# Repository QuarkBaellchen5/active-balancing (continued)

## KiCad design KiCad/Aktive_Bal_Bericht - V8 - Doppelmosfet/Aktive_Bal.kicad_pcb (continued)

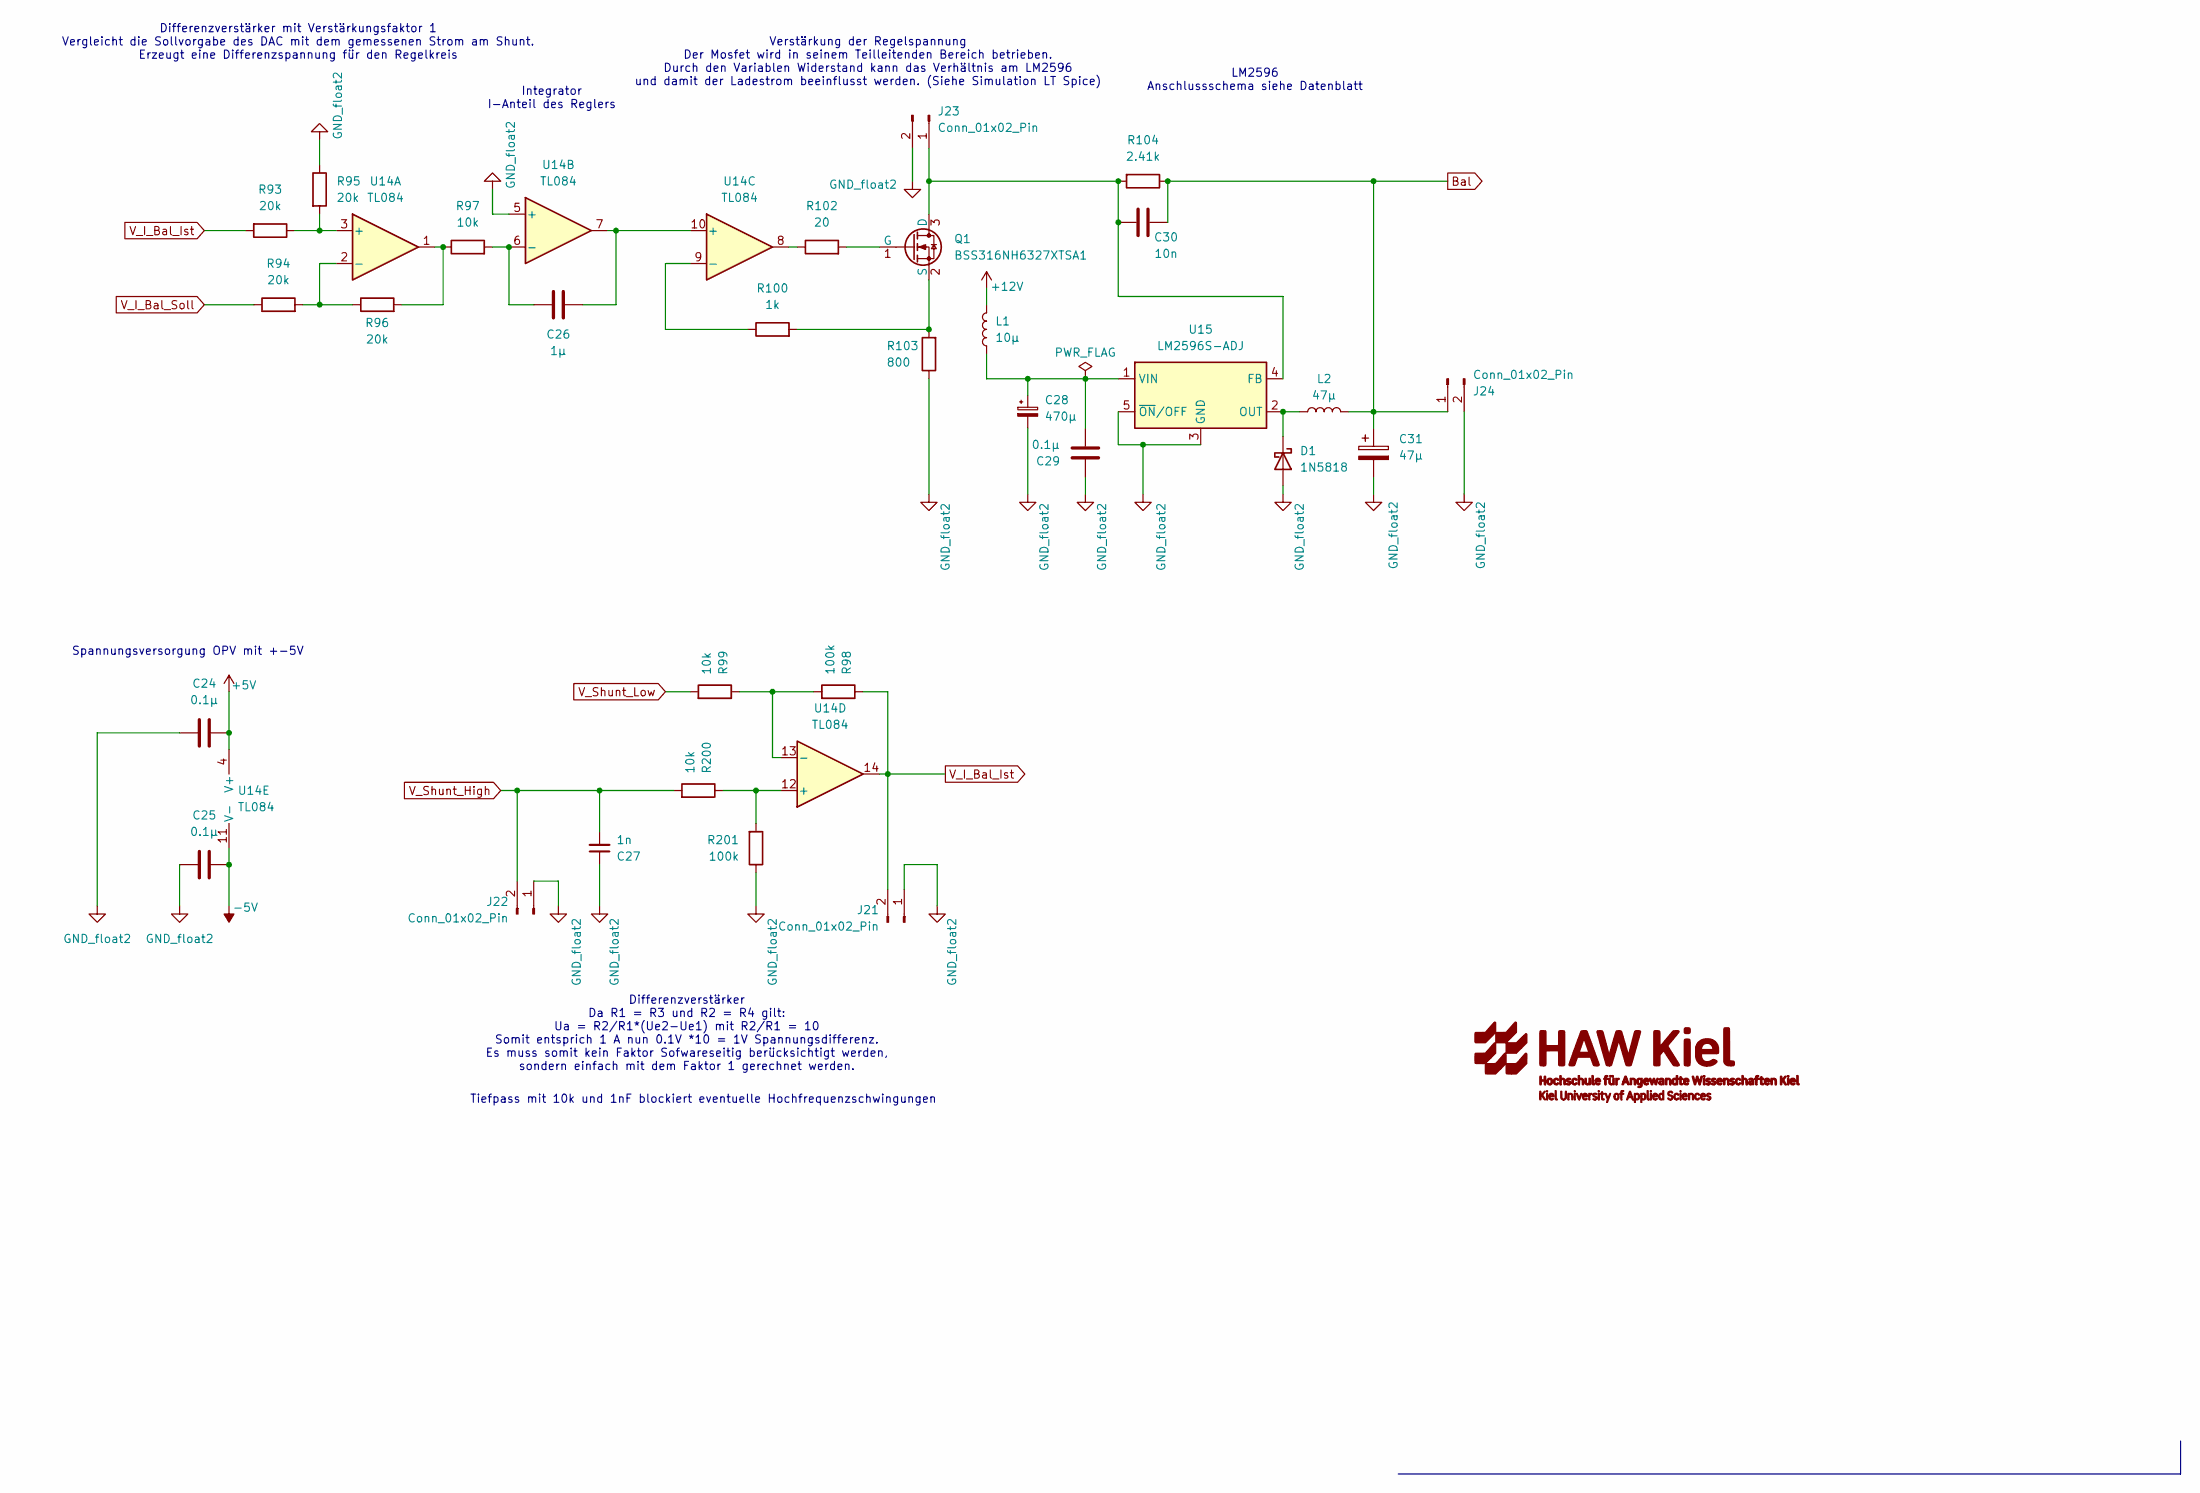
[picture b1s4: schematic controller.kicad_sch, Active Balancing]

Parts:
C24, C25, C29: 0.1µ; C_0805_2012Metric
C26: 1µ; C_0805_2012Metric
C27: 1n; C_0805_2012Metric
C28: 470µ; C_Elec_8x10.2
C30: 10n; C_0805_2012Metric
C31: 47µ; CP_Elec_5x5.3
D1: 1N5818; D_SMA
J21, J22, J23, J24: Conn_01x02_Pin; PinHeader_1x02_P2.54mm_Vertical
L1: 10µ; NRS6045
L2: 47µ; L_Bourns_SRR1260
Q1: BSS316NH6327XTSA1; SOT-23
R93, R94, R95, R96: 20k; R_0805_2012Metric
R97, R99, R200: 10k; R_0805_2012Metric
R98, R201: 100k; R_0805_2012Metric
R100: 1k; R_0805_2012Metric
R102: 20; R_0805_2012Metric
R103: 800; R_0805_2012Metric
R104: 2.41k; R_0805_2012Metric
U14: TL084; SOIC-14_3.9x8.7mm_P1.27mm
U15: LM2596S-ADJ; LM2596_5T

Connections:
+5V: C24.2, U14.4 (V+); also elsewhere on the board
+12V: L1.1; also elsewhere on the board
-5V: C25.2, U14.11 (V-); also elsewhere on the board
Bal: C30.2, C31.1, J24.1, L2.2, R104.1; also elsewhere on the board
GND_float2: C24.1, C25.1, C27.1, C28.2, C29.1, C31.2, D1.2 (A), J21.1, J22.1, J23.2, J24.2, R95.1, R103.1, R201.1, U14.5 (+), U15.3 (GND), U15.5 (~ON/OFF); also elsewhere on the board
unnamed: D1.1 (K), L2.1, U15.2 (OUT)
unnamed: C30.1, J23.1, Q1.3 (D), R104.2, U15.4 (FB)
unnamed: Q1.1 (G), R102.2
unnamed: Q1.2 (S), R100.2, R103.2
unnamed: R96.2, R97.1, U14.1
unnamed: R102.1, U14.8
unnamed: R93.1, R95.2, U14.3 (+)
unnamed: R94.2, R96.1, U14.2 (-)
unnamed: C26.1, R97.2, U14.6 (-)
unnamed: C26.2, U14.7, U14.10 (+)
unnamed: R100.1, U14.9 (-)
unnamed: R200.1, R201.2, U14.12 (+)
unnamed: R98.2, R99.1, U14.13 (-)
unnamed: C28.1, C29.2, L1.2, U15.1 (VIN)
V_I_Bal_Ist: J21.2, R93.2, R98.1, U14.14
V_I_Bal_Soll: R94.1; also elsewhere on the board
V_Shunt_High: C27.2, J22.2, R200.2; also elsewhere on the board
V_Shunt_Low: R99.2; also elsewhere on the board

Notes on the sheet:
Differenzverstärker Da R1 = R3 und R2 = R4 gilt: Ua = R2/R1*(Ue2-Ue1) mit R2/R1 = 10 Somit entsprich 1 A nun 0.1V *10 = 1V Spannungsdifferenz. Es muss somit kein Faktor Sofwareseitig berücksichtigt werden, sondern einfach mit dem Faktor 1 gerechnet werden.
LM2596 Anschlussschema siehe Datenblatt
Integrator I-Anteil des Reglers
Differenzverstärker mit Verstärkungsfaktor 1 Vergleicht die Sollvorgabe des DAC mit dem gemessenen Strom am Shunt. Erzeugt eine Differenzspannung für den Regelkreis
Verstärkung der Regelspannung Der Mosfet wird in seinem Teilleitenden Bereich betrieben. Durch den Variablen Widerstand kann das Verhältnis am LM2596 und damit der Ladestrom beeinflusst werden. (Siehe Simulation LT Spice)
Spannungsversorgung OPV mit +-5V
Tiefpass mit 10k und 1nF blockiert eventuelle Hochfrequenzschwingungen

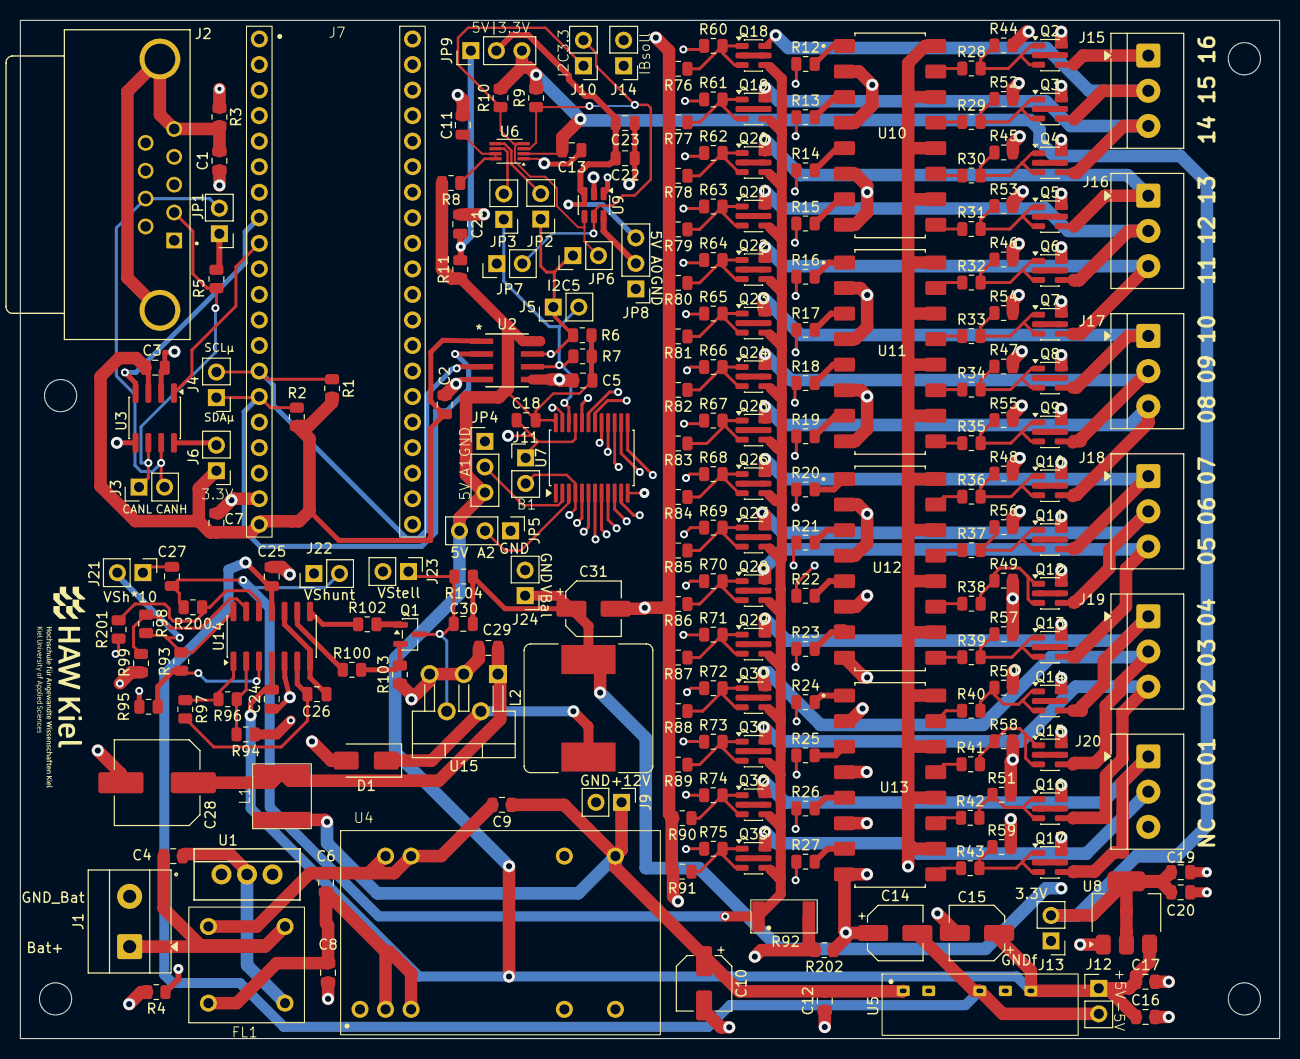
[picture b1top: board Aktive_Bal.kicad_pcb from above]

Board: 4 copper layers, 125.2 x 101.3 mm, 225 parts (0 on the bottom side), 180 nets.

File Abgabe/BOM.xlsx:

Reference | Qty | Value | DNP | Exclude from BOM | Exclude from Board | Footprint | Datasheet
C1,C8,C9,C27 | 4 | 1n |  |  |  | Capacitor_SMD:C_0805_2012Metric
C2,C3,C5,C7,C13,C17,C18,C19,C23,C24,C25,C29 | 12 | 0.1µ |  |  |  | Capacitor_SMD:C_0805_2012Metric
C4,C6 | 2 | 2.2µ |  |  |  | Capacitor_SMD:C_0805_2012Metric
C10,C31 | 2 | 47µ |  |  |  | Capacitor_SMD:CP_Elec_5x5.3
C11 | 1 | 0.1n |  |  |  | Capacitor_SMD:C_0805_2012Metric
C12 | 1 | 4.7µ |  |  |  | Capacitor_SMD:C_0805_2012Metric
C14,C15 | 2 | 10µ |  |  |  | Capacitor_SMD:CP_Elec_5x5.3
C16,C20,C22 | 3 | 10µ tantal |  |  |  | Capacitor_SMD:C_0805_2012Metric
C21 | 1 | 10µ |  |  |  | Capacitor_SMD:C_0805_2012Metric
C26 | 1 | 1µ |  |  |  | Capacitor_SMD:C_0805_2012Metric
C28 | 1 | 470µ |  |  |  | Capacitor_SMD:C_Elec_8x10.2
C30 | 1 | 10n |  |  |  | Capacitor_SMD:C_0805_2012Metric
D1 | 1 | 1N5818 |  |  |  | Diode_SMD:D_SMA | http://www.vishay.com/docs/88525/1n5817.pdf
FL1 | 1 | Choke_CommonMode_TCK_050 |  |  |  | Aktive_Bal_Footprints:common mode choke foot | https://productfinder.pulseelectronics.com/api/open/product-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
J1 | 1 | Screw_Terminal_01x02 |  |  |  | Aktive_Bal_Footprints:1-2-5mmTerminalBlock_MetzConnect_Type055_RT01502HDWU_1x02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
J2 | 1 | A-DF_09_A_KG-T4S |  |  |  | Aktive_Bal_Footprints:ASSMANN_A-DF_09_A_KG-T4S | file://C:\Users\maria\Documents\Uni\Semester 6\Projektarbeit\active-balancing\K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
J3,J4,J5,J6,J9,J10,J11,J12,J13,J14,J21,J22,J23,J24 | 14 | Conn_01x02_Pin |  |  |  | Connector_PinHeader_2.54mm:PinHeader_1x02_P2.54mm_Vertical
J7 | 1 | Sockel_BluePill |  |  |  | Aktive_Bal_Footprints:SockelBluepill Dupont leisten
J15,J16,J17,J18,J19,J20 | 6 | Screw_Terminal_01x03 |  |  |  | Aktive_Bal_Footprints:TerminalBlock_4Ucon_1x03_P3.50mm_Horizontal_3d
JP1,JP6,JP7 | 3 | Jumper_2_Open |  |  |  | Connector_PinHeader_2.54mm:PinHeader_1x02_P2.54mm_Vertical
JP2,JP3 | 2 | Jumper_2_Bridged |  |  |  | Connector_PinHeader_2.54mm:PinHeader_1x02_P2.54mm_Vertical
L1 | 1 | 10µ |  |  |  | Aktive_Bal_Footprints:NRS6045
L2 | 1 | 47µ |  |  |  | Inductor_SMD:L_Bourns_SRR1260
Q1 | 1 | BSS316NH6327XTSA1 |  |  |  | Package_TO_SOT_SMD:SOT-23
Q2,Q3,Q4,Q5,Q6,Q7,Q8,Q9,Q10,Q11,Q12,Q13,Q14,Q15,Q16,Q17,Q18,Q19,Q20,Q21,Q22,Q23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 | 32 | Q_Dual_NMOS_G1S2G2D2S1D1 |  |  |  | Package_TO_SOT_SMD:SOT-23-6
R1,R2,R9,R10 | 4 | 4.7k |  |  |  | Resistor_SMD:R_0805_2012Metric
R3 | 1 | 1Meg |  |  |  | Resistor_SMD:R_0805_2012Metric
R4,R44,R45,R46,R47,R48,R49,R50,R51,R52,R53,R54,R55,R56,R57,R58,R59,R76,R77,R78,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 | 35 | 100k |  |  |  | Resistor_SMD:R_0805_2012Metric
R5 | 1 | 120 |  |  |  | Resistor_SMD:R_0805_2012Metric
R6,R7 | 2 | 2.2k |  |  |  | Resistor_SMD:R_0805_2012Metric
R8 | 1 | 200k |  |  |  | Resistor_SMD:R_0805_2012Metric
R11 | 1 | 10 |  |  |  | Resistor_SMD:R_0805_2012Metric
R12,R13,R14,R15,R16,R17,R18,R19,R20,R21,R22,R23,R24,R25,R26,R27 | 16 | 390 |  |  |  | Resistor_SMD:R_0805_2012Metric
R28,R29,R30,R31,R32,R33,R34,R35,R36,R37,R38,R39,R40,R41,R42,R43,R60,R61,R62,R63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 | 32 | 330 |  |  |  | Resistor_SMD:R_0805_2012Metric
R92 | 1 | CMP-R100-1.0 |  |  |  | Aktive_Bal_Footprints:CMP-R100-1.0
R93,R94,R95,R96 | 4 | 20k |  |  |  | Resistor_SMD:R_0805_2012Metric
R97,R99,R200 | 3 | 10k |  |  |  | Resistor_SMD:R_0805_2012Metric
R100 | 1 | 1k |  |  |  | Resistor_SMD:R_0805_2012Metric
R102 | 1 | 20 |  |  |  | Resistor_SMD:R_0805_2012Metric
R103 | 1 | 800 |  |  |  | Resistor_SMD:R_0805_2012Metric
R104 | 1 | 2.41k |  |  |  | Resistor_SMD:R_0805_2012Metric
R202 | 1 | 0 |  |  |  | Resistor_SMD:R_0805_2012Metric
U1 | 1 | RFP12N10L |  |  |  | Aktive_Bal_Footprints:TO-220AB_ONS | RFP12N10L
U2 | 1 | ADUM1250ARZ-RL7 |  |  |  | Aktive_Bal_Footprints:ADUM1250ARZ-RL7_R_8_ADI-M | https://www.analog.com/media/en/technical-documentation/data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
U3 | 1 | SN65HVD233 |  |  |  | Package_SO:SOIC-8_3.9x4.9mm_P1.27mm | http://www.ti.com/lit/ds/symlink/sn65hvd234.pdf
U4 | 1 | SCW20C-12 |  |  |  | Aktive_Bal_Footprints:SCW20C-12 | file://C:\Users\maria\Documents\Uni\Semester 6\Projektarbeit\active-balancing\K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
U5 | 1 | EC1SA16N |  |  |  | Aktive_Bal_Footprints:EC1SA16N | file://C:\Users\maria\Documents\Uni\Semester 6\Projektarbeit\active-balancing\K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
U6 | 1 | PCA9306DC |  |  |  | Package_SO:VSSOP-8_2.3x2mm_P0.5mm | https://www.nxp.com/docs/en/data-sheet/PCA9306.pdf
U7 | 1 | PCF8575CDB |  |  |  | Aktive_Bal_Footprints:PCF8575CDB_SSOP-24_5.3x8.2mm_P0.65mm | https://www.ti.com/lit/gpn/pcf8575c
U8 | 1 | LM1117MP-3.3 |  |  |  | Package_TO_SOT_SMD:SOT-223-3_TabPin2 | http://www.ti.com/lit/ds/symlink/lm1117.pdf
U9 | 1 | MCP4725xxx-xCH |  |  |  | Package_TO_SOT_SMD:SOT-23-6 | http://ww1.microchip.com/downloads/en/DeviceDoc/22039d.pdf
U10,U11,U12,U13 | 4 | LTV-847S |  |  |  | Aktive_Bal_Footprints:SOIC254P1016X460-16N | file://C:\Users\maria\Documents\Uni\Semester 6\Projektarbeit\active-balancing\K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
U14 | 1 | TL084 |  |  |  | Package_SO:SOIC-14_3.9x8.7mm_P1.27mm | http://www.ti.com/lit/ds/symlink/tl081.pdf
U15 | 1 | LM2596S-ADJ |  |  |  | Aktive_Bal_Footprints:LM2596_5T | http://www.ti.com/lit/ds/symlink/lm2596.pdf

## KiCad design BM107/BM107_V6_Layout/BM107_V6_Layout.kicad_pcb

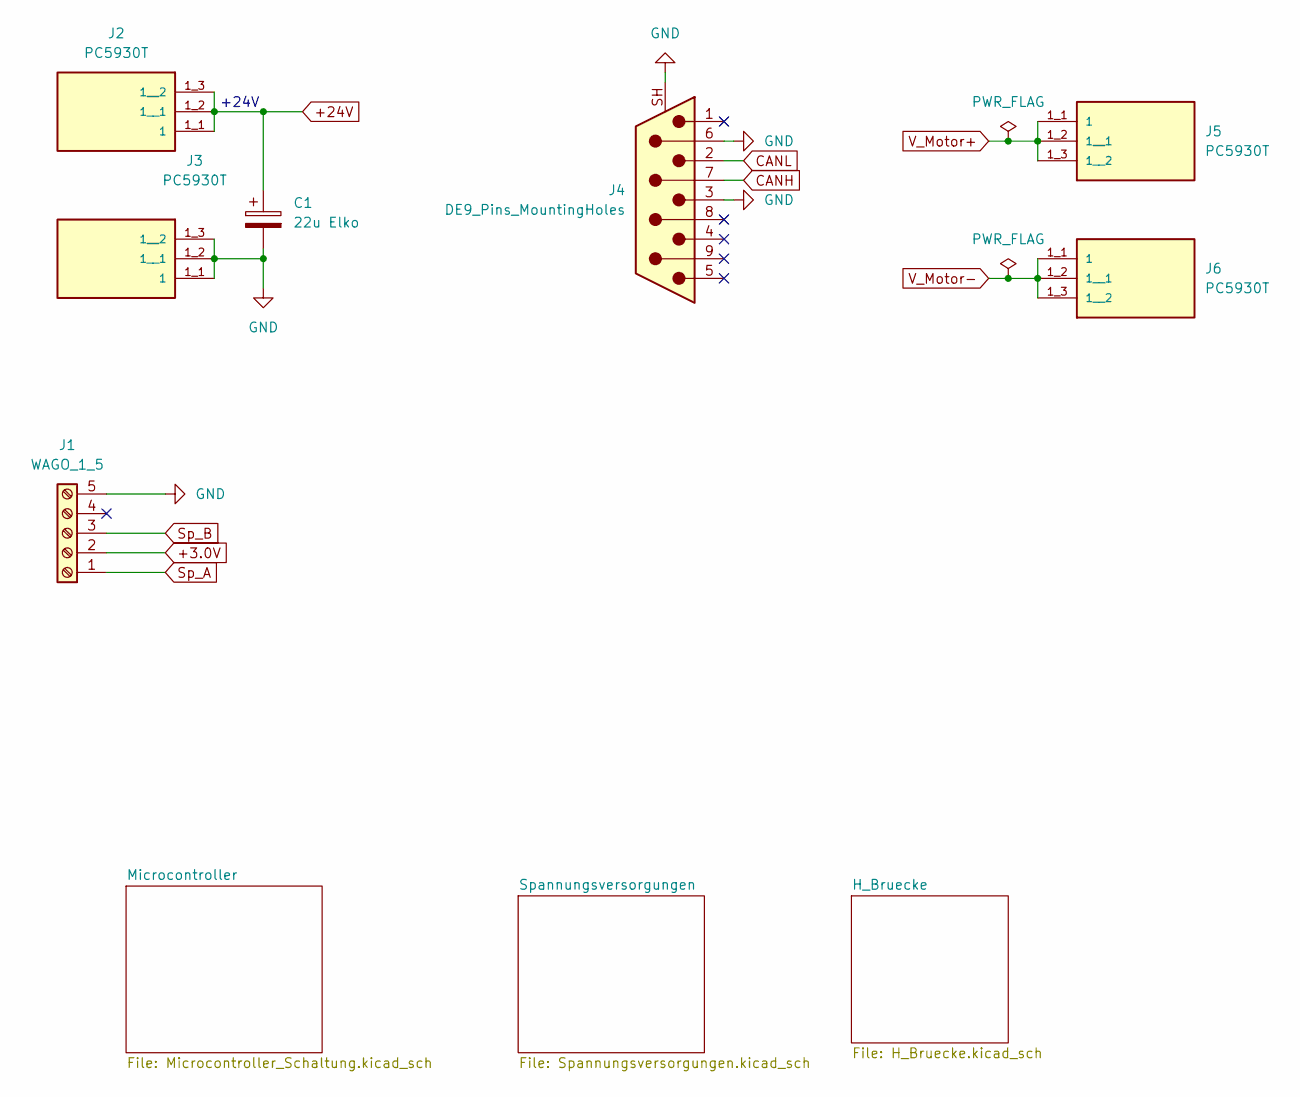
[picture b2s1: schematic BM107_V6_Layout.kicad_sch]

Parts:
C1: 22u Elko; CP_Elec_5x5.3
J1: WAGO_1_5; Wago_734-135_1x05_P3.50mm_Vertical
J2, J3, J5, J6: PC5930T; ANDERSONPOWER_PC5930T; PARTREV 4
J4: DE9_Pins_MountingHoles; D_SUB9_Stecker

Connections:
+3.0V: J1.2; also elsewhere on the board
+24V: C1.1, J2.1_1 (1), J2.1_2 (1__1), J2.1_3 (1__2); also elsewhere on the board
CANH: J4.7; also elsewhere on the board
CANL: J4.2; also elsewhere on the board
GND: C1.2, J1.5, J3.1_1 (1), J3.1_2 (1__1), J3.1_3 (1__2), J4.3, J4.6, J4.SH (PAD); also elsewhere on the board
Sp_A: J1.1; also elsewhere on the board
Sp_B: J1.3; also elsewhere on the board
V_Motor+: J5.1_1 (1), J5.1_2 (1__1), J5.1_3 (1__2); also elsewhere on the board
V_Motor-: J6.1_1 (1), J6.1_2 (1__1), J6.1_3 (1__2); also elsewhere on the board

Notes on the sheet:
+24V

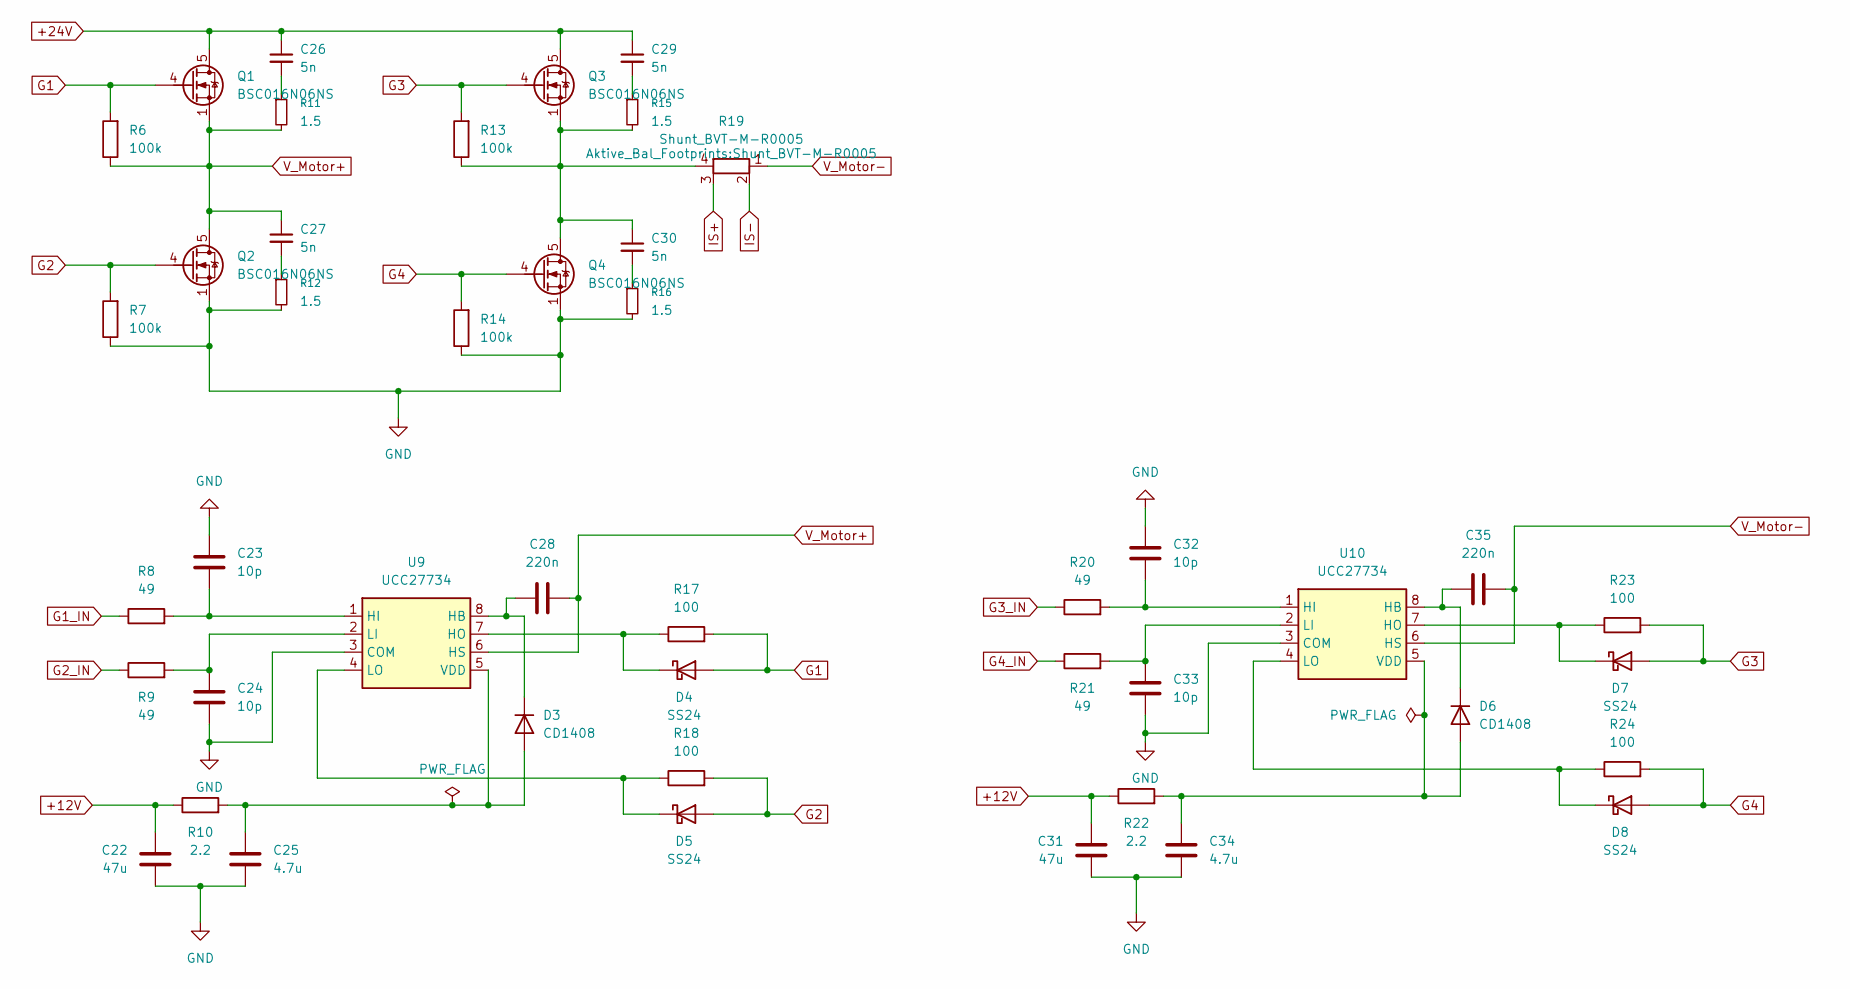
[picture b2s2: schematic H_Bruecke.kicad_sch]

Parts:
C22, C31: 47u; C_0805_2012Metric
C23, C24, C32, C33: 10p; C_0805_2012Metric
C25, C34: 4.7u; C_0805_2012Metric
C26, C27, C29, C30: 5n; C_0805_2012Metric
C28, C35: 220n; C_0805_2012Metric
D3, D6: CD1408; CD1408_Footprint
D4, D5, D7, D8: SS24; D_SMA
Q1, Q2, Q3, Q4: BSC016N06NS
R6, R7, R13, R14: 100k; R_0805_2012Metric
R8, R9, R20, R21: 49; R_0805_2012Metric
R10, R22: 2.2; R_0805_2012Metric
R11, R12, R15, R16: 1.5; R_0805_2012Metric
R17, R18, R23, R24: 100; R_0805_2012Metric
R19: Shunt_BVT-M-R0005
U9, U10: UCC27734; SOIC-8_3.9x4.9mm_P1.27mm_UCC27734

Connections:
+12V: C22.1, C31.1, R10.1, R22.1; also elsewhere on the board
+24V: C26.1, C29.1, Q1.5 (D), Q3.5 (D); also elsewhere on the board
G1: D4.2 (A), Q1.4 (G), R6.2, R17.2
G1_IN: R8.1; also elsewhere on the board
G2: D5.2 (A), Q2.4 (G), R7.2, R18.2
G2_IN: R9.1; also elsewhere on the board
G3: D7.2 (A), Q3.4 (G), R13.2, R23.2
G3_IN: R20.1; also elsewhere on the board
G4: D8.2 (A), Q4.4 (G), R14.2, R24.2
G4_IN: R21.1; also elsewhere on the board
GND: C22.2, C23.1, C24.2, C25.2, C31.2, C32.1, C33.2, C34.2, Q2.1 (S), Q2.2 (S), Q2.3 (S), Q4.1 (S), Q4.2 (S), Q4.3 (S), R7.1, R12.2, R14.1, R16.2, U9.3 (COM), U10.3 (COM); also elsewhere on the board
IS+: R19.3; also elsewhere on the board
IS-: R19.2; also elsewhere on the board
unnamed: C26.2, R11.1
unnamed: C27.2, R12.1
unnamed: C29.2, R15.1
unnamed: C30.2, R16.1
unnamed: C25.1, D3.2 (A), R10.2, U9.5 (VDD)
unnamed: C28.1, D3.1 (K), U9.8 (HB)
unnamed: D4.1 (K), R17.1, U9.7 (HO)
unnamed: D5.1 (K), R18.1, U9.4 (LO)
unnamed: C34.1, D6.2 (A), R22.2, U10.5 (VDD)
unnamed: C35.1, D6.1 (K), U10.8 (HB)
unnamed: D7.1 (K), R23.1, U10.7 (HO)
unnamed: D8.1 (K), R24.1, U10.4 (LO)
unnamed: C30.1, Q3.1 (S), Q3.2 (S), Q3.3 (S), Q4.5 (D), R13.1, R15.2, R19.4
unnamed: C23.2, R8.2, U9.1 (HI)
unnamed: C24.1, R9.2, U9.2 (LI)
unnamed: C32.2, R20.2, U10.1 (HI)
unnamed: C33.1, R21.2, U10.2 (LI)
V_Motor+: C27.1, C28.2, Q1.1 (S), Q1.2 (S), Q1.3 (S), Q2.5 (D), R6.1, R11.2, U9.6 (HS); also elsewhere on the board
V_Motor-: C35.2, R19.1, U10.6 (HS); also elsewhere on the board

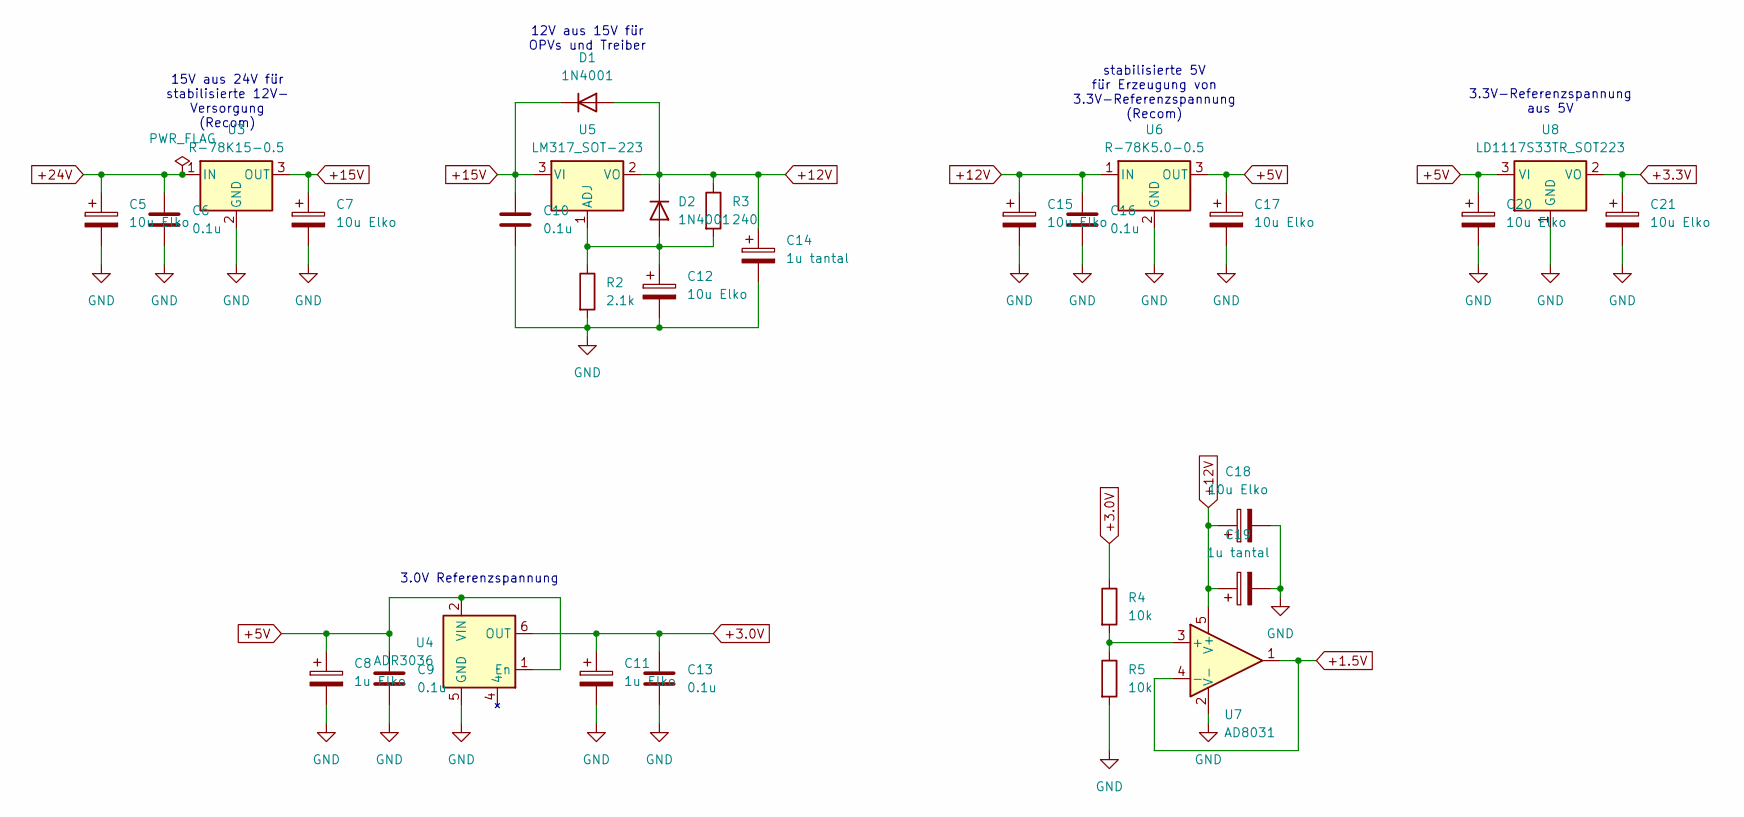
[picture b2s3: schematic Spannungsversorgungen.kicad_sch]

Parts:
C5, C7, C12, C15, C17, C18, C20, C21: 10u Elko; CP_Elec_5x5.3
C6, C9, C10, C13, C16: 0.1u; C_0805_2012Metric
C8, C11: 1u Elko; CP_Elec_5x5.3
C14, C19: 1u tantal; C_0805_2012Metric
D1, D2: 1N4001; D_DO-41_SOD81_P10.16mm_Horizontal
R2: 2.1k; R_0805_2012Metric
R3: 240; R_0805_2012Metric
R4, R5: 10k; R_0805_2012Metric
U3: R-78K15-0.5; Converter_DCDC_RECOM_R-78E-0.5_THT
U4: ADR3036; MSOP-8_3x3mm_P0.65mm
U5: LM317_SOT-223; SOT-223-3_TabPin2
U6: R-78K5.0-0.5; Converter_DCDC_RECOM_R-78E-0.5_THT
U7: AD8031; SOT-23-5
U8: LD1117S33TR_SOT223; SOT-223-3_TabPin2

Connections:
+1.5V: U7.1, U7.4 (-); also elsewhere on the board
+3.0V: C11.1, C13.1, R4.1, U4.6 (OUT); also elsewhere on the board
+3.3V: C21.1, U8.2 (VO); also elsewhere on the board
+5V: C8.1, C9.1, C17.1, C20.1, U4.1 (En), U4.2 (VIN), U6.3 (OUT), U8.3 (VI); also elsewhere on the board
+12V: C14.1, C15.1, C16.1, C18.1, C19.1, D1.2 (A), D2.1 (K), R3.1, U5.2 (VO), U6.1 (IN), U7.5 (V+); also elsewhere on the board
+15V: C7.1, C10.1, D1.1 (K), U3.3 (OUT), U5.3 (VI)
+24V: C5.1, C6.1, U3.1 (IN); also elsewhere on the board
GND: C5.2, C6.2, C7.2, C8.2, C9.2, C10.2, C11.2, C12.2, C13.2, C14.2, C15.2, C16.2, C17.2, C18.2, C19.2, C20.2, C21.2, R2.2, R5.2, U3.2 (GND), U4.5 (GND), U6.2 (GND), U7.2 (V-), U8.1 (GND); also elsewhere on the board
unnamed: C12.1, D2.2 (A), R2.1, R3.2, U5.1 (ADJ)
unnamed: R4.2, R5.1, U7.3 (+)

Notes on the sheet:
12V aus 15V für OPVs und Treiber
stabilisierte 5V für Erzeugung von 3.3V-Referenzspannung (Recom)
3.3V-Referenzspannung aus 5V
3.0V Referenzspannung
15V aus 24V für stabilisierte 12V- Versorgung (Recom)

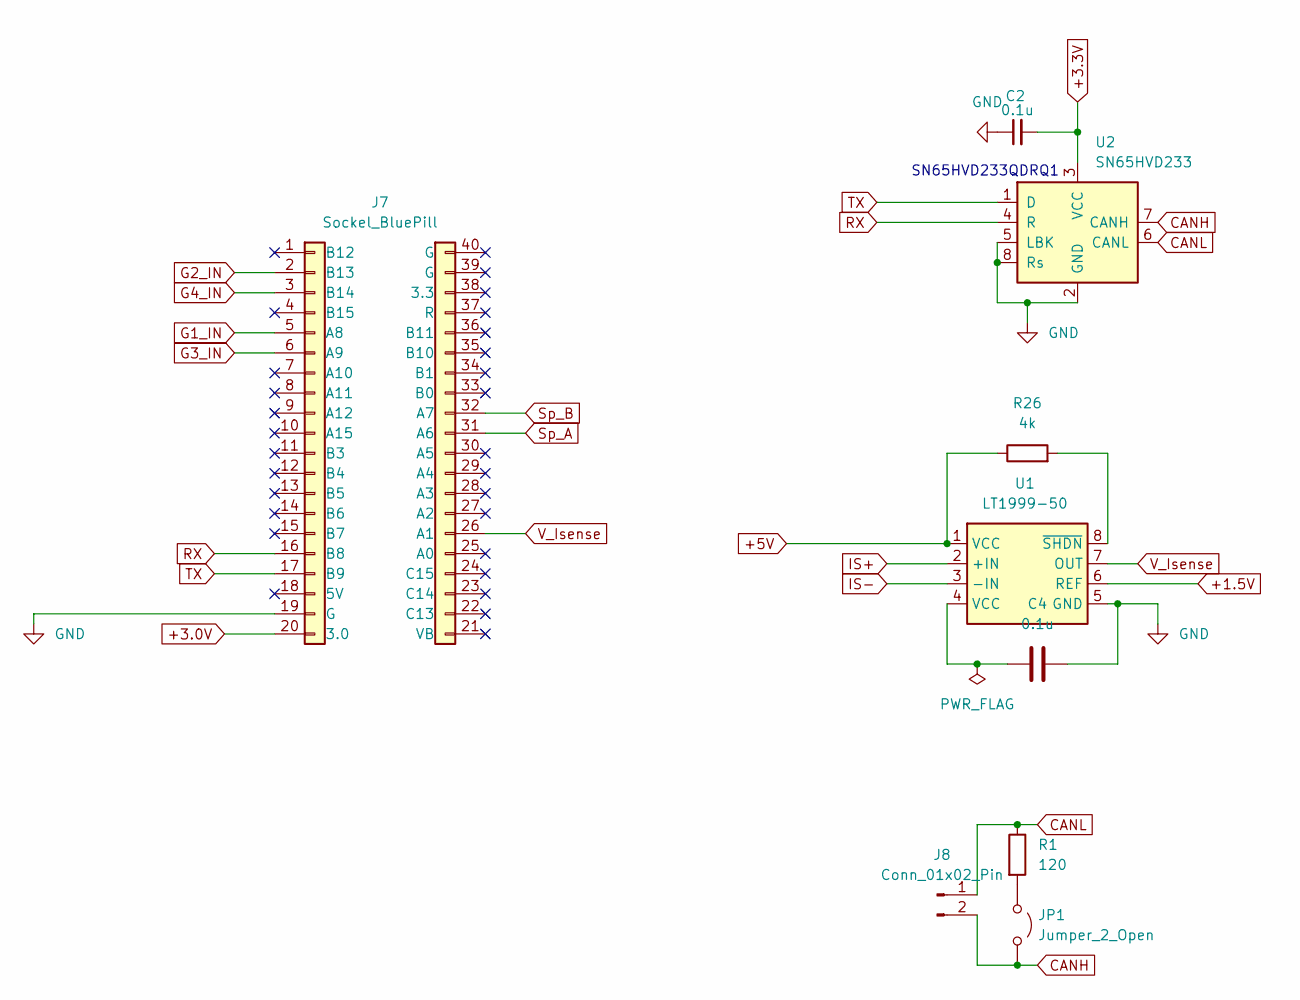
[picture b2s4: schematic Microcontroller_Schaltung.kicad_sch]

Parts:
C2, C4: 0.1u; C_0805_2012Metric
J7: Sockel_BluePill; SockelBluepill Dupont leisten
J8: Conn_01x02_Pin; PinHeader_1x02_P2.54mm_Vertical
JP1: Jumper_2_Open; SolderJumper-2_P1.3mm_Open_TrianglePad1.0x1.5mm
R1: 120; R_0805_2012Metric
R26: 4k; R_0805_2012Metric
U1: LT1999-50; MSOP-8_3x3mm_P0.65mm
U2: SN65HVD233; SOIC-8_3.9x4.9mm_P1.27mm

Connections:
+1.5V: U1.6 (REF); also elsewhere on the board
+3.0V: J7.20 (3.0); also elsewhere on the board
+3.3V: C2.2, U2.3 (VCC); also elsewhere on the board
+5V: R26.1, U1.1 (VCC); also elsewhere on the board
CANH: J8.2, JP1.2 (B), U2.7 (CANH); also elsewhere on the board
CANL: J8.1, R1.1, U2.6 (CANL); also elsewhere on the board
G1_IN: J7.5 (A8); also elsewhere on the board
G2_IN: J7.2 (B13); also elsewhere on the board
G3_IN: J7.6 (A9); also elsewhere on the board
G4_IN: J7.3 (B14); also elsewhere on the board
GND: C2.1, C4.2, J7.19 (G), U1.5 (GND), U2.2 (GND), U2.5 (LBK), U2.8 (Rs); also elsewhere on the board
IS+: U1.2 (+IN); also elsewhere on the board
IS-: U1.3 (-IN); also elsewhere on the board
unnamed: C4.1, U1.4 (VCC)
unnamed: JP1.1 (A), R1.2
unnamed: R26.2, U1.8 (~SHDN)
RX: J7.16 (B8), U2.4 (R)
Sp_A: J7.31 (A6); also elsewhere on the board
Sp_B: J7.32 (A7); also elsewhere on the board
TX: J7.17 (B9), U2.1 (D)
V_Isense: J7.26 (A1), U1.7 (OUT)

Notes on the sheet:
SN65HVD233QDRQ1

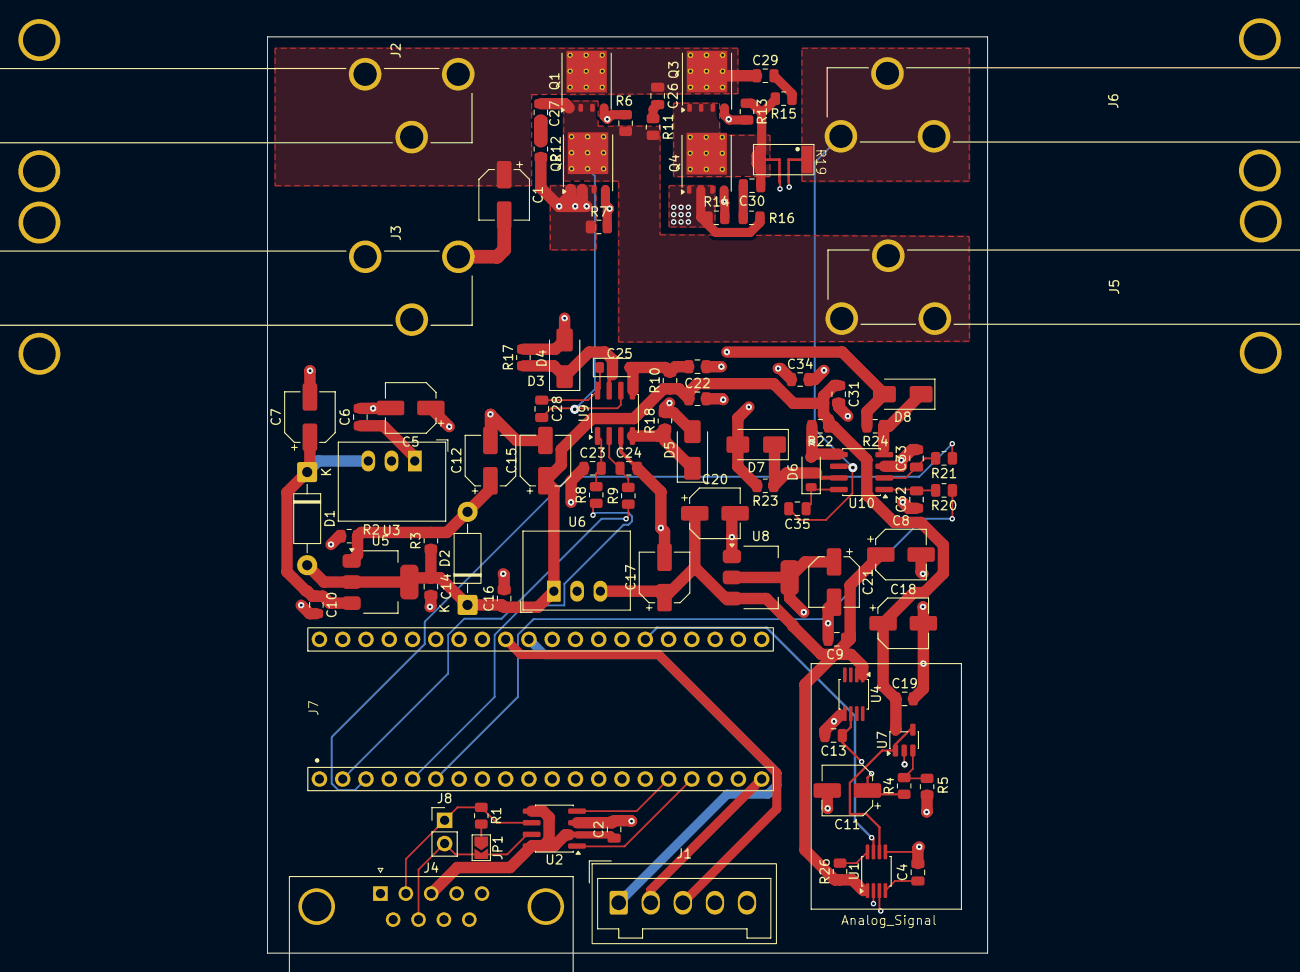
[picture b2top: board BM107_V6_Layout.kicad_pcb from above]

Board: 4 copper layers, 78.6 x 100.0 mm, 90 parts (0 on the bottom side), 49 nets.

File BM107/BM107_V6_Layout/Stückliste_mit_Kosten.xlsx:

Reference | Qty | Value | DNP | Exclude from BOM | Exclude from Board | Footprint | Stückzahl für 10 Platinen | Kosten Stückzahl 10 (Preis pro 10 Stk*Stückzahl pro Platine | Stückzahl für 100 Platinen | Kosten Stückzahl 100 (Preis pro 100 Stk*Stückzahl pro Platine) | Quelle
C1 | 1 | 22u Elko |  |  |  | Capacitor_SMD:CP_Elec_5x5.3 | 10 | 5.65 | 100 | 38.619999999999997 | https://www.digikey.de/de/products/detail/chemi-con/HHXD350A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
C2,C4,C6,C9,C10,C13,C16 | 7 | 0.1u |  |  |  | Capacitor_SMD:C_0805_2012Metric | 70 | 5.32 | 700 | 32.550000000000004 | https://www.digikey.de/de/products/detail/taiyo-yuden/GMK212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
C3,C23,C24,C32,C33 | 5 | 10p |  |  |  | Capacitor_SMD:C_0805_2012Metric | 50 | 10.95 | 500 | 72.5 | https://www.digikey.de/de/products/detail/johanson-technolog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
C5,C7,C12,C15,C17,C18,C20,C21 | 8 | 10u Elko |  |  |  | Capacitor_SMD:CP_Elec_5x5.3 | 80 | 71.84 | 800 | 5.0335999999999999 | https://www.digikey.de/de/products/detail/panasonic-industry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
C8,C11 | 2 | 1u Elko |  |  |  | Capacitor_SMD:CP_Elec_5x5.3 | 20 | 36 | 200 | 360 | https://www.reichelt.de/de/de/shop/produkt/smd-elko_1_f_50v_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
C14,C19 | 2 | 1u tantal |  |  |  | Capacitor_SMD:C_0805_2012Metric | 20 | 27.7 | 200 | 209.92 | https://www.digikey.de/de/products/detail/kyocera-avx/TLCR10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
C22,C31 | 2 | 47u |  |  |  | Capacitor_SMD:C_0805_2012Metric | 20 | 9.32 | 200 | 62.94 | https://www.digikey.de/de/products/detail/panasonic-industry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
C25,C34 | 2 | 4.7u |  |  |  | Capacitor_SMD:C_0805_2012Metric | 20 | 1.7 | 200 | 10.48 | https://www.digikey.de/de/products/detail/samsung-electro-me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
C26,C27,C29,C30 | 4 | 5n |  |  |  | Capacitor_SMD:C_0805_2012Metric | 40 | 3.4799999999999995 | 400 | 21.4 | https://www.digikey.de/de/products/detail/taiyo-yuden/GMK212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
C28,C35 | 2 | 220n |  |  |  | Capacitor_SMD:C_0805_2012Metric | 20 |  | 200
D1,D2 | 2 | 1N4001 |  |  |  | Diode_THT:D_DO-41_SOD81_P10.16mm_Horizontal | 20 |  | 200
D3,D6 | 2 | CD1408 |  |  |  | Aktive_Bal_Footprints:CD1408_Footprint | 20 |  | 200
D4,D5,D7,D8 | 4 | SS24 |  |  |  | Diode_SMD:D_SMA | 40 |  | 400
J1,J2,J5,J6 | 4 | PC5930T |  |  |  | Aktive_Bal_Footprints:PC5930T_Footprint | 40 |  | 400
J3 | 1 | WAGO_1_5 |  |  |  | Connector_Wago:Wago_734-135_1x05_P3.50mm_Vertical | 10 |  | 100
J4 | 1 | DE9_Pins_MountingHoles |  |  |  | Aktive_Bal_Footprints:D_SUB9_Stecker | 10 |  | 100
J7 | 1 | Sockel_BluePill |  |  |  | Aktive_Bal_Footprints:SockelBluepill Dupont leisten | 10 |  | 100
J8 | 1 | Conn_01x02_Pin |  |  |  | Connector_PinHeader_2.54mm:PinHeader_1x02_P2.54mm_Vertical | 10 |  | 100
JP1 | 1 | Jumper_2_Open |  |  |  | Jumper:SolderJumper-2_P1.3mm_Open_TrianglePad1.0x1.5mm | 10 |  | 100
Q1,Q2,Q3,Q4 | 4 | BSC016N06NS |  |  |  | Package_TO_SOT_SMD:TDSON-8-1 | 40 |  | 400
R1 | 1 | 120 |  |  |  | Resistor_SMD:R_0805_2012Metric | 10 |  | 100
R2 | 1 | 2.1k |  |  |  | Resistor_SMD:R_0805_2012Metric | 10 |  | 100
R3 | 1 | 240 |  |  |  | Resistor_SMD:R_0805_2012Metric | 10 |  | 100
R4,R5 | 2 | R |  |  |  | Resistor_SMD:R_0805_2012Metric | 20 |  | 200
R6,R7,R13,R14 | 4 | 100k |  |  |  | Resistor_SMD:R_0805_2012Metric | 40 |  | 400
R8,R9,R20,R21 | 4 | 49 |  |  |  | Resistor_SMD:R_0805_2012Metric | 40 |  | 400
R10,R22 | 2 | 2.2 |  |  |  | Resistor_SMD:R_0805_2012Metric | 20 |  | 200
R11,R12,R15,R16 | 4 | 1.5 |  |  |  | Resistor_SMD:R_0805_2012Metric | 40 |  | 400
R17,R18,R23,R24 | 4 | 100 |  |  |  | Resistor_SMD:R_0805_2012Metric | 40 |  | 400
R26 | 1 | Shunt_BVT-M-R0005 |  |  |  | Aktive_Bal_Footprints:Shunt_BVT-M-R0005 | 10 |  | 100
U1 | 1 | SN65HVD233 |  |  |  | Package_SO:SOIC-8_3.9x4.9mm_P1.27mm | 10 |  | 100
U2 | 1 | LT1999-50 |  |  |  | Package_SO:MSOP-8_3x3mm_P0.65mm | 10 |  | 100
U3 | 1 | R-78K15-0.5 |  |  |  | Converter_DCDC:Converter_DCDC_RECOM_R-78E-0.5_THT | 10 |  | 100
U4 | 1 | ADR3036 |  |  |  | Package_SO:MSOP-8_3x3mm_P0.65mm | 10 |  | 100
U5 | 1 | LM317_SOT-223 |  |  |  | Package_TO_SOT_SMD:SOT-223-3_TabPin2 | 10 |  | 100
U6 | 1 | R-78K5.0-0.5 |  |  |  | Converter_DCDC:Converter_DCDC_RECOM_R-78E-0.5_THT | 10 |  | 100
U7 | 1 | AD8031 |  |  |  | Package_TO_SOT_SMD:SOT-23-5 | 10 |  | 100
U8 | 1 | LD1117S33TR_SOT223 |  |  |  | Package_TO_SOT_SMD:SOT-223-3_TabPin2 | 10 |  | 100
U9,U10 | 2 | UCC27734 |  |  |  | Aktive_Bal_Footprints:SOIC-8_3.9x4.9mm_P1.27mm_UCC27734 | 20 |  | 200
